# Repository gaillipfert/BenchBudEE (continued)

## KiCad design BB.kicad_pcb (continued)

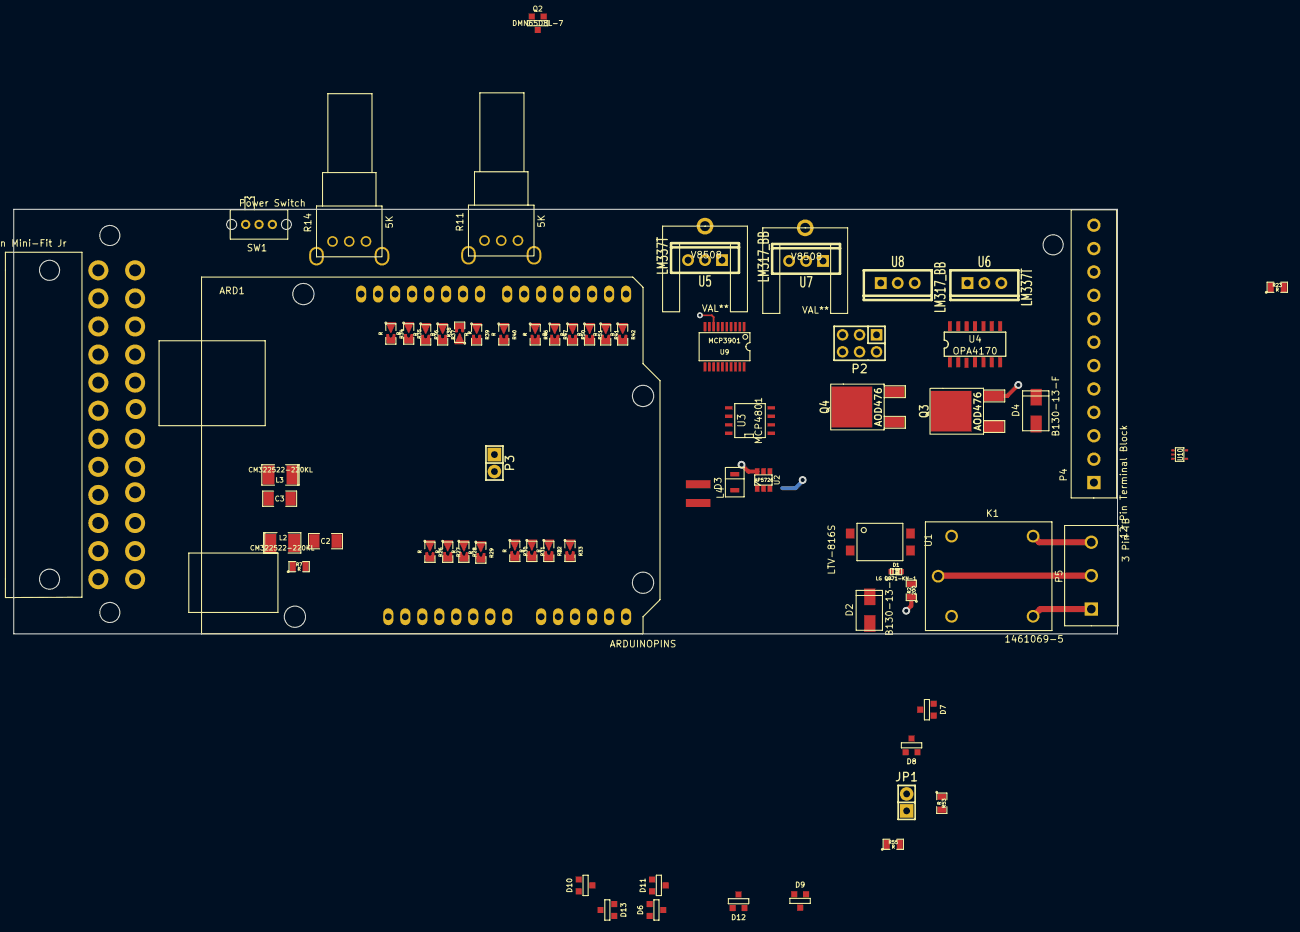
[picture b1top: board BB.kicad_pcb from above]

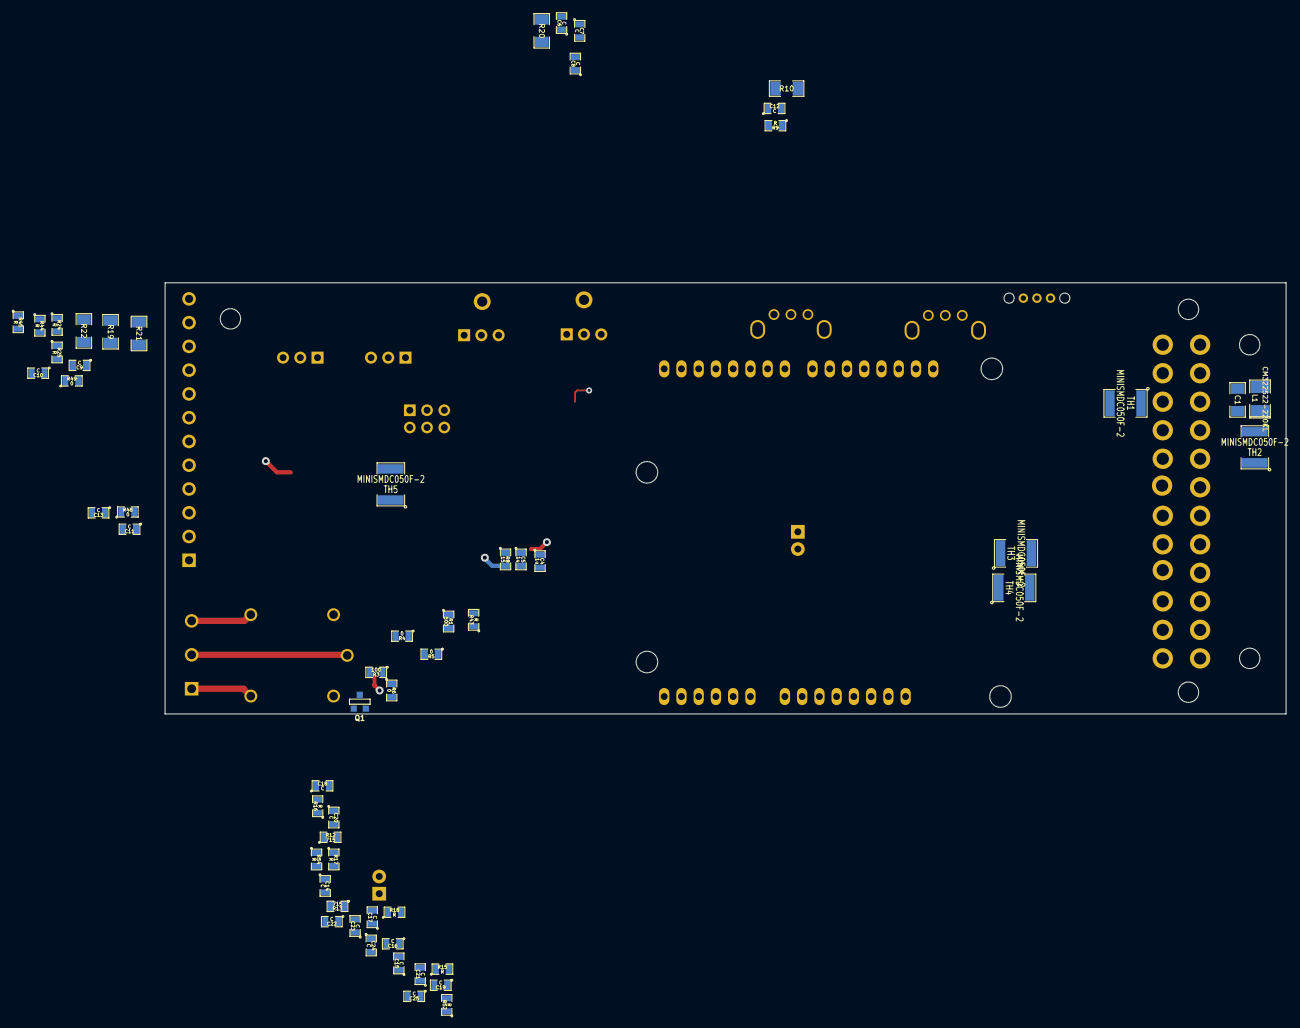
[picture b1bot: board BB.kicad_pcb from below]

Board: 4 copper layers, 165.1 x 63.5 mm, 129 parts (57 on the bottom side), 102 nets.

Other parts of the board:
3_mm, 3_mm#2, 3_mm#3: VAL**; 3_mm
JP1: JUMPER; Pin_Header_Straight_2x01
V8508, V8508#2: VAL**; V8508

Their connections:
AGND: JP1.2; also elsewhere on the board
GND: JP1.1; also elsewhere on the board

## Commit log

2014-02-01 new file: BB-cache.lib new file: BB.kicad_pcb new file: BB.pro new file: BB.sch
2014-02-10 Addedd Week three changes to Bench BudEE. Arduino.sch BB.bck BB.dcm BB.lib Fan.sch LED_Driver.sch Power.sch PowerAdjustmentMonitor.sch Relay.sch TerminalBlock.sch Thermocouple.sch
2014-02-11 Week 3 changes. new file: Arduino.sch modified: BB-cache.lib new file: BB.bck new file: BB.dcm new file: BB.lib modified: BB.sch new file: Fan.sch new file: LED_Driver.sch new file: Power.sch new fil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
2014-02-13 modified: BB.pro
2014-02-14 Adding the readme file.
2014-02-19 Added Relay module footprints.
2014-02-24 Associated and placed thermocouple, terminal, arduino, fan driver, power protection modules.
2014-03-03 Layout sessions 1-4.
